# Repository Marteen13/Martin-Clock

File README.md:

# Martin-Clock
 My first HPS clock

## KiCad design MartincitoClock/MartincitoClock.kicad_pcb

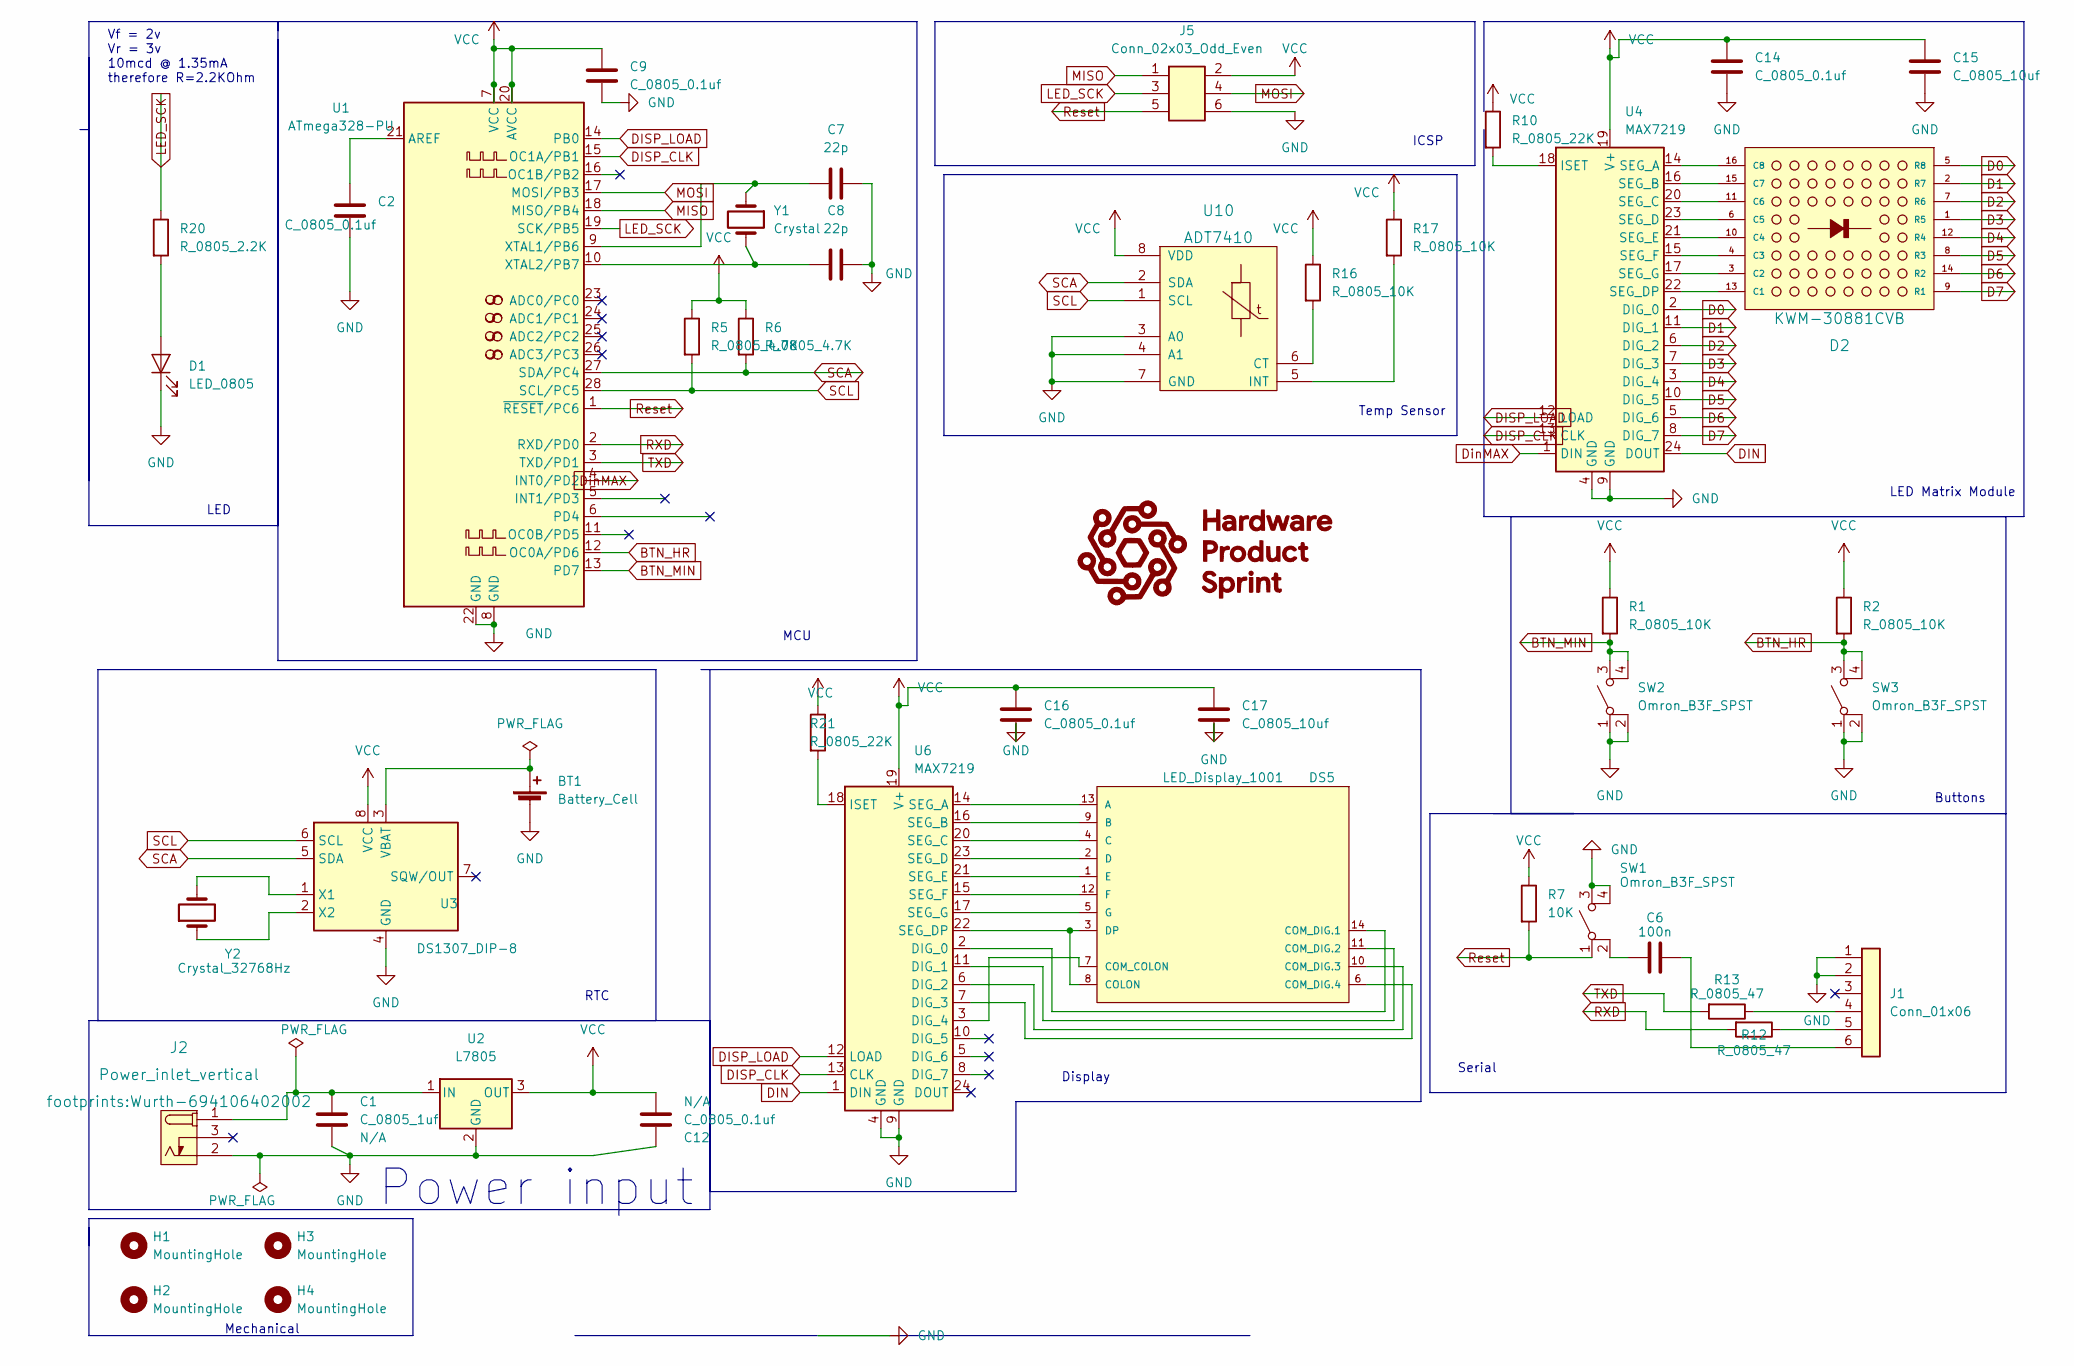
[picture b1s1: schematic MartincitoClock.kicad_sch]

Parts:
BT1: Battery_Cell; BatteryHolder_Keystone_106_1x20mm; MPN BS-7; Digikey PN BS-7-ND
C1: C_0805_1uf; C_0805_2012Metric; Voltage N/A; Tolerance N/A; MPN 08055C104KAT2A; Digikey PN 478-1395-1-ND
C2, C9, C12, C14, C16: C_0805_0.1uf; C_0805_2012Metric; Voltage N/A; Tolerance N/A; MPN 08055C104KAT2A; Digikey PN 478-1395-1-ND
C6: 100n; C_0805_2012Metric; Voltage N/A; Tolerance N/A; MPN 08055C104KAT2A; Digikey PN 478-1395-1-ND
C7, C8: 22p; C_0805_2012Metric; Voltage N/A; Tolerance N/A; MPN 08055C104KAT2A; Digikey PN 478-1395-1-ND
C15, C17: C_0805_10uf; C_0805_2012Metric; Voltage N/A; Tolerance N/A; MPN GRM21BR61E106KA73L; Digikey PN 490-5523-1-ND
D1: LED_0805; LED_0805_2012Metric; MPN 150080RS75000; Digikey PN 732-4984-1-ND
D2: KWM-30881CVB; MPN KWM-30881CVB; Digikey PN N/A
DS5: LED_Display_1001; Adafruit-1001-0-0-MFG; forward voltage 3.2V; reverse voltage 5V; mouser part number 485-1001; digikey description WHITE 7-SEGMENT CLOCK DISPLAY
H1, H2, H3, H4: MountingHole; MountingHole_3.2mm_M3
J1: Conn_01x06; PinHeader_1x06_P2.54mm_Vertical; MPN 61300611121; Digikey PN 732-5319-ND
J2: Power_inlet_vertical; Wurth-694106402002; MPN 694106402002; Digikey PN 732-5931-ND
J5: Conn_02x03_Odd_Even; PinHeader_2x03_P2.54mm_Vertical; MPN PRPC003DAAN-RC; Digikey PN S2011EC-03-ND
R1, R2, R16, R17: R_0805_10K; R_0805_2012Metric; Tolerance N/A; MPN RC0805FR-0710KL; Digikey PN 311-10.0KCRCT-ND
R5, R6: R_0805_4.7K; R_0805_2012Metric; Tolerance N/A; MPN RC0805FR-074K7L; Digikey PN 311-4.70KCRCT-ND
R7: 10K; R_0805_2012Metric; Tolerance N/A; MPN RC0805FR-0710KL; Digikey PN 311-10.0KCRCT-ND
R10, R21: R_0805_22K; R_0805_2012Metric; Tolerance N/A; MPN RC0805FR-0722KL; Digikey PN 311-22.0KCRCT-ND
R12, R13: R_0805_47; R_0805_2012Metric; Tolerance N/A; Mouser PN N/A; Digikey PN RC0805FR-0747RL
R20: R_0805_2.2K; R_0805_2012Metric; Tolerance N/A; MPN N/A; Digikey PN 311-2.20KCRCT-ND
SW1, SW2, SW3: Omron_B3F_SPST; SW_SPST_Omron_B3FS-100xP; MPN B3FS-1000P; Digikey PN SW423CT-ND
U1: ATmega328-PU; DIP-28_W7.62mm; MPN ED281DT; Digikey PN ED3050-5-ND
U2: L7805; TO-252-2; MPN L7805CDT-TR; Digikey PN 497-7255-1-ND
U3: DS1307_DIP-8; DIP-8_W7.62mm; MPN A 08-LC-TT; Digikey PN AE9986-ND
U4, U6: MAX7219; DIP-24_W7.62mm; MPN ED241DT; Digikey PN ED3049-5-ND
U10: ADT7410; SOIC-8_3.9x4.9mm_P1.27mm; MPN ADT7410TRZ; Digikey PN ADT7410TRZ-ND
Y1: Crystal; Crystal_SMD_2Pin_3.2x1.5mm; MPN Q 0,032768-JTX310-12,5-20-T1-HMR-50K-LF; Digikey PN 1908-1314-1-ND
Y2: Crystal_32768Hz; Crystal_SMD_2Pin_3.2x1.5mm; MPN Q 0,032768-JTX310-12,5-20-T1-HMR-50K-LF; Digikey PN 1908-1314-1-ND

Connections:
BTN_HR: R2.2, SW3.3 (B), SW3.4 (B), U1.12 (OC0A/PD6)
BTN_MIN: R1.2, SW2.3 (B), SW2.4 (B), U1.13 (PD7)
D0: D2.5 (R8), U4.2 (DIG_0)
D1: D2.2 (R7), U4.11 (DIG_1)
D2: D2.7 (R6), U4.6 (DIG_2)
D3: D2.1 (R5), U4.7 (DIG_3)
D4: D2.12 (R4), U4.3 (DIG_4)
D5: D2.8 (R3), U4.10 (DIG_5)
D6: D2.14 (R2), U4.5 (DIG_6)
D7: D2.9 (R1), U4.8 (DIG_7)
DIN: U4.24 (DOUT), U6.1 (DIN)
DISP_CLK: U1.15 (OC1A/PB1), U4.13 (CLK), U6.13 (CLK)
DISP_LOAD: U1.14 (PB0), U4.12 (LOAD), U6.12 (LOAD)
DinMAX: U1.4 (INT0/PD2), U4.1 (DIN)
GND: BT1.2 (-), C1.1, C2.2, C7.1, C8.1, C9.2, C12.1, C14.2, C15.2, C16.2, C17.2, D1.1 (K), J1.1, J1.2, J2.2 (OUT), J5.6, SW1.3 (B), SW1.4 (B), SW2.1 (A), SW2.2 (A), SW3.1 (A), SW3.2 (A), U1.8 (GND), U1.22 (GND), U2.2 (GND), U3.4 (GND), U4.4 (GND), U4.9 (GND), U6.4 (GND), U6.9 (GND), U10.3 (A0), U10.4 (A1), U10.7 (GND)
LED_SCK: J5.3, R20.1, U1.19 (SCK/PB5)
MISO: J5.1, U1.18 (MISO/PB4)
MOSI: J5.4, U1.17 (MOSI/PB3)
unnamed: BT1.1 (+), U3.3 (VBAT)
unnamed: C1.2, J2.1 (POLE), U2.1 (IN)
unnamed: C2.1, U1.21 (AREF)
unnamed: C6.1, J1.6
unnamed: C6.2, SW1.2 (A)
unnamed: C7.2, U1.9 (XTAL1/PB6), Y1.1
unnamed: C8.2, U1.10 (XTAL2/PB7), Y1.2
unnamed: D1.2 (A), R20.2
unnamed: D2.11 (C6), U4.20 (SEG_C)
unnamed: DS5.1 (E), U6.21 (SEG_E)
unnamed: DS5.2 (D), U6.23 (SEG_D)
unnamed: DS5.3 (DP), DS5.8 (COLON), U6.22 (SEG_DP)
unnamed: DS5.4 (C), U6.20 (SEG_C)
unnamed: DS5.5 (G), U6.17 (SEG_G)
unnamed: DS5.6 (COM_DIG.4), U6.7 (DIG_3)
unnamed: DS5.7 (COM_COLON), U6.3 (DIG_4)
unnamed: DS5.9 (B), U6.16 (SEG_B)
unnamed: DS5.10 (COM_DIG.3), U6.6 (DIG_2)
unnamed: DS5.11 (COM_DIG.2), U6.11 (DIG_1)
unnamed: DS5.12 (F), U6.15 (SEG_F)
unnamed: DS5.13 (A), U6.14 (SEG_A)
unnamed: DS5.14 (COM_DIG.1), U6.2 (DIG_0)
unnamed: J1.4, R13.1
unnamed: J1.5, R12.1
unnamed: R10.2, U4.18 (ISET)
unnamed: R16.2, U10.6 (CT)
unnamed: R17.2, U10.5 (INT)
unnamed: R21.2, U6.18 (ISET)
unnamed: U3.1 (X1), Y2.2
unnamed: U3.2 (X2), Y2.1
unnamed: D2.16 (C8), U4.14 (SEG_A)
unnamed: D2.4 (C3), U4.15 (SEG_F)
unnamed: D2.15 (C7), U4.16 (SEG_B)
unnamed: D2.3 (C2), U4.17 (SEG_G)
unnamed: D2.10 (C4), U4.21 (SEG_E)
unnamed: D2.13 (C1), U4.22 (SEG_DP)
unnamed: D2.6 (C5), U4.23 (SEG_D)
RXD: R12.2, U1.2 (RXD/PD0)
Reset: J5.5, R7.2, SW1.1 (A), U1.1 (~RESET/PC6)
SCA: R6.2, U1.27 (SDA/PC4), U3.5 (SDA), U10.2 (SDA)
SCL: R5.2, U1.28 (SCL/PC5), U3.6 (SCL), U10.1 (SCL)
TXD: R13.2, U1.3 (TXD/PD1)
VCC: C9.1, C12.2, C14.1, C15.1, C16.1, C17.1, J5.2, R1.1, R2.1, R5.1, R6.1, R7.1, R10.1, R16.1, R17.1, R21.1, U1.7 (VCC), U1.20 (AVCC), U2.3 (OUT), U3.8 (VCC), U4.19 (V+), U6.19 (V+), U10.8 (VDD)

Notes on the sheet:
Temp Sensor
Buttons
Vf = 2v Vr = 3v 10mcd @ 1.35mA therefore R=2.2KOhm
ICSP
Display
Power input
LED Matrix Module
RTC
Mechanical
Serial
LED
MCU

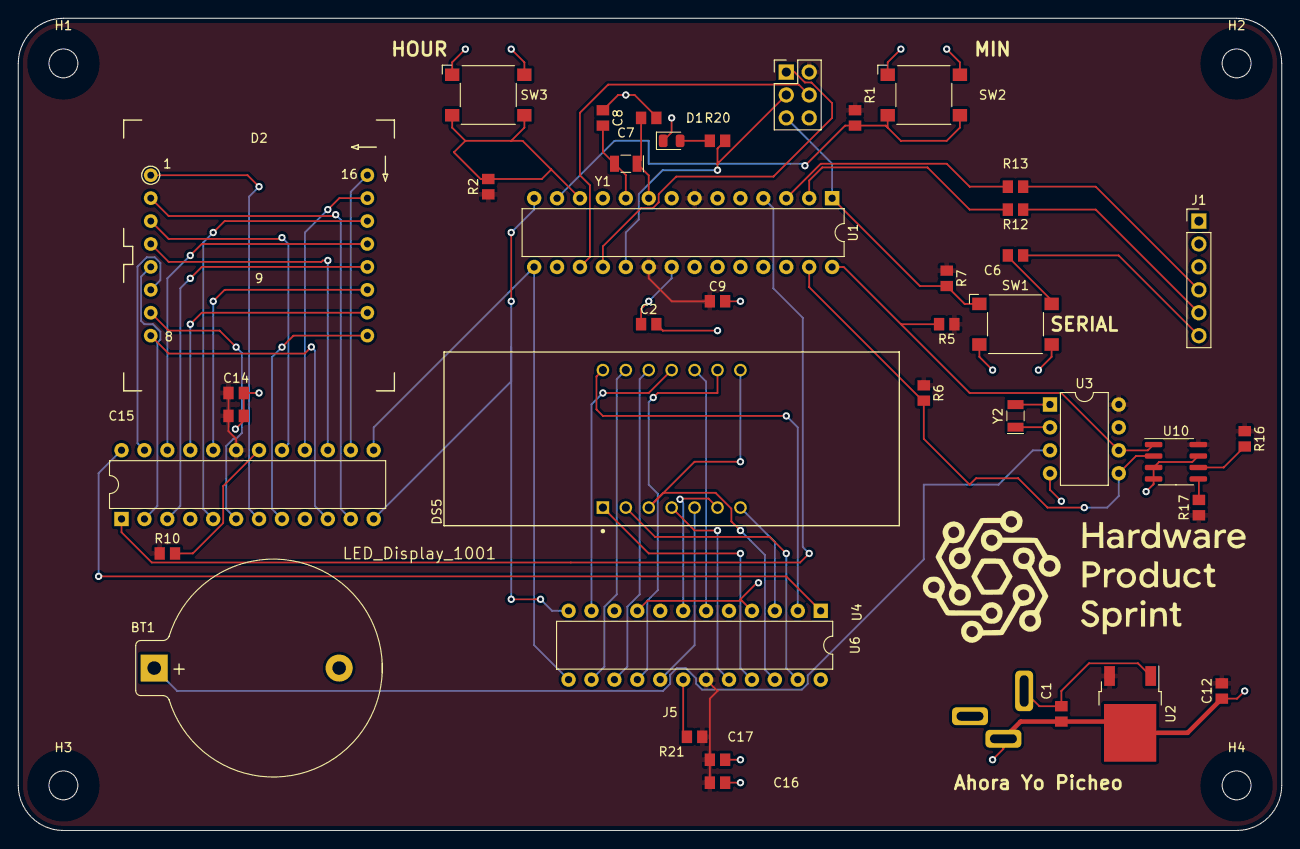
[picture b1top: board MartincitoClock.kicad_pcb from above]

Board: 2 copper layers, 140.0 x 90.0 mm, 45 parts (1 on the bottom side), 61 nets.

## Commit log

2022-06-03 My First Design Commit
2022-06-13 Week 1 Deliverable
2022-06-20 Week 2 Deliverable
2022-06-20 Week 2 Code
2022-06-27 Week 3 Deliverables
2022-07-05 Week 5
2022-07-19 Week 6
    Week 6 Deliverable
2022-07-21 Final Gerber
2022-07-22 Final
2022-07-23 Revised Final
